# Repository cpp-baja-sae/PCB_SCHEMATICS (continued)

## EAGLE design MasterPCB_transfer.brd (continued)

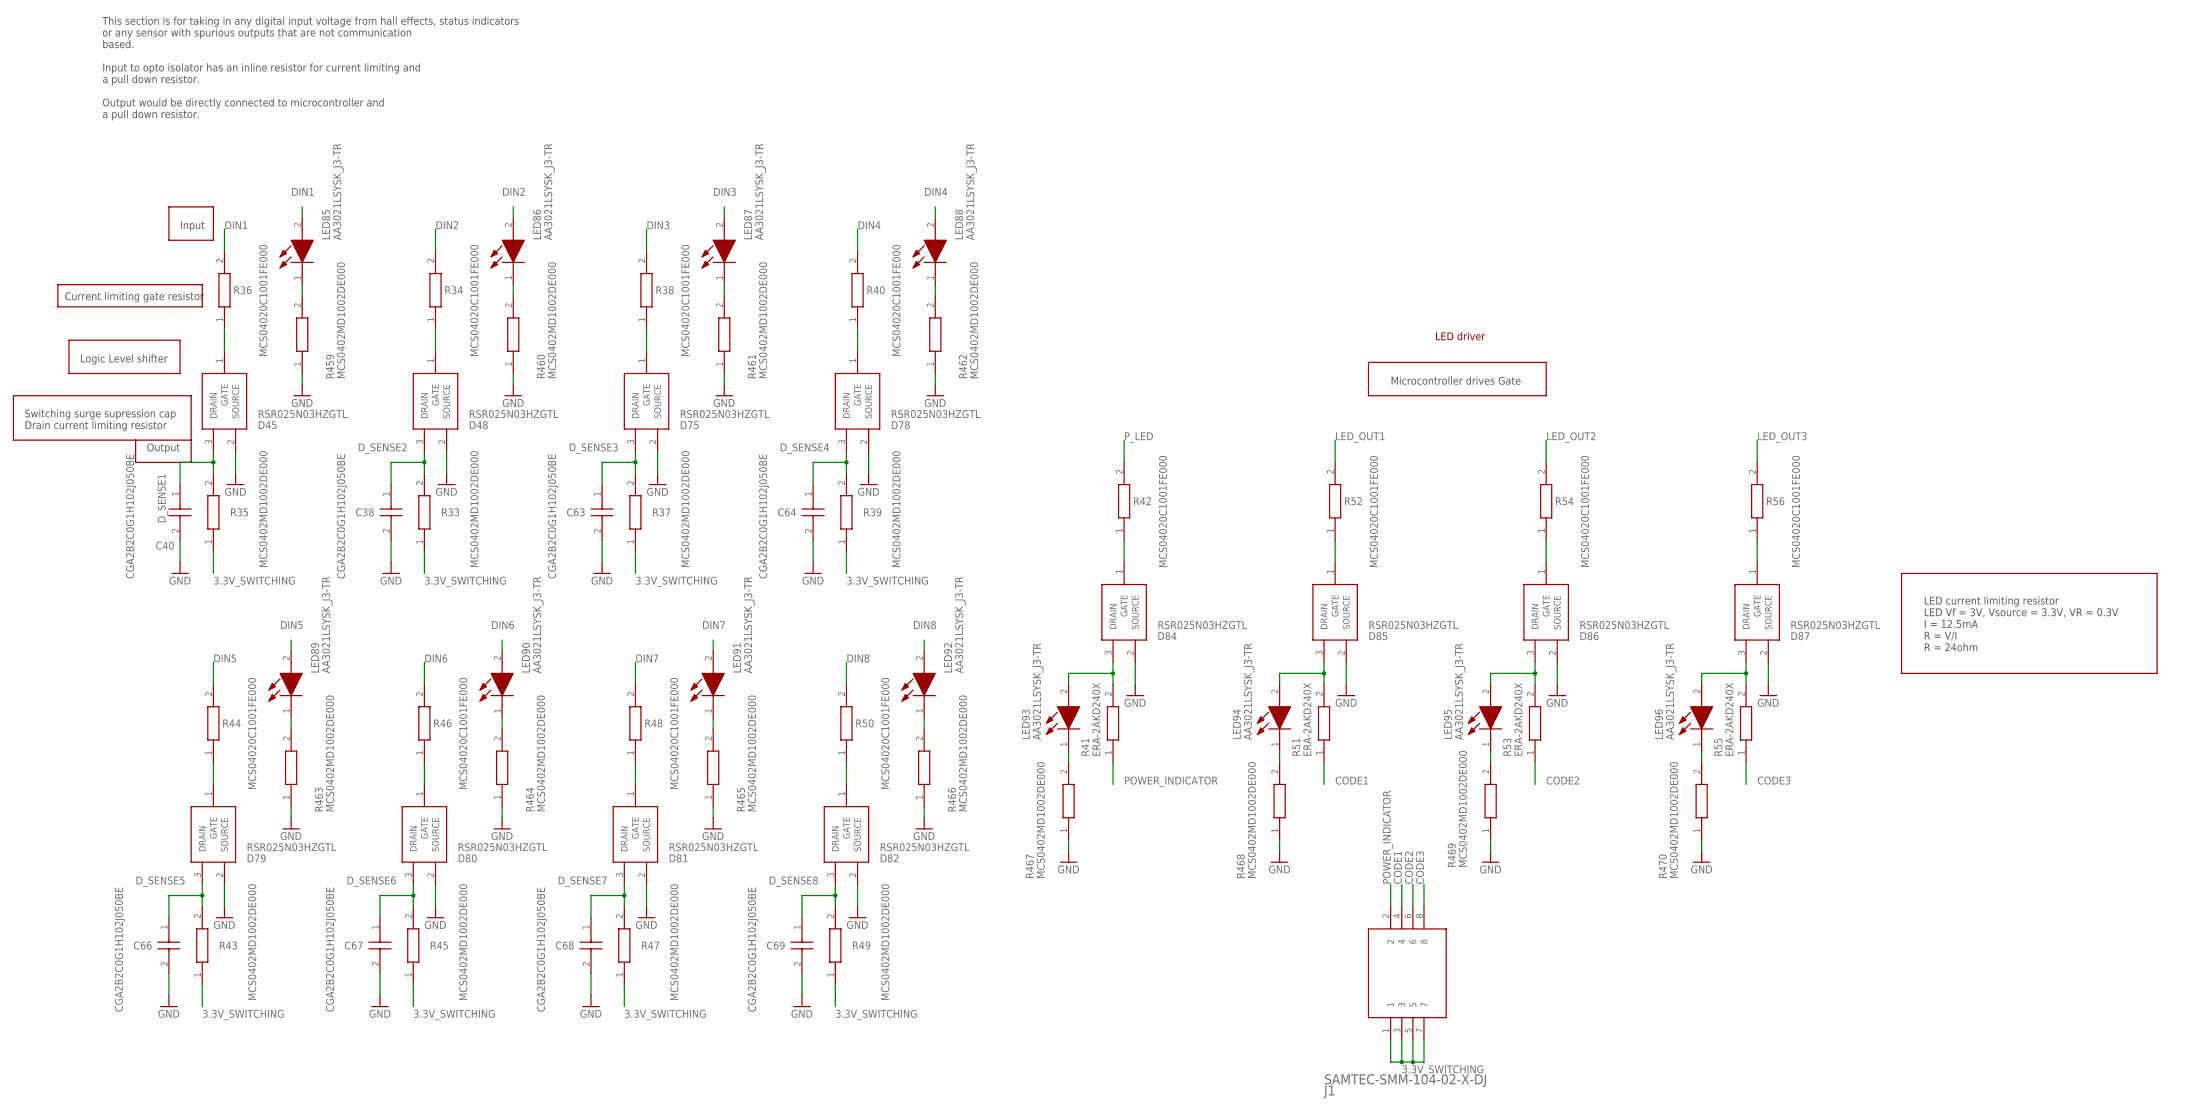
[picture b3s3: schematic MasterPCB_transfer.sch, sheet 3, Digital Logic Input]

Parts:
C38, C40, C63, C64, C66, C67, C68, C69: CGA2B2C0G1H102J050BE; CAPC1005X55N
D45, D48, D75, D78, D79, D80, D81, D82, D84, D85, D86, D87: RSR025N03HZGTL; SOT95P280X100-3N
J1: SAMTEC-SMM-104-02-X-DJ; SAMTEC-SMM-104-02-X-D
LED85, LED86, LED87, LED88, LED89, LED90, LED91, LED92, LED93, LED94, LED95, LED96: AA3021LSYSK_J3-TR; AA3021LSYSKJ3TR
R33, R35, R37, R39, R43, R45, R47, R49, R459, R460, R461, R462, R463, R464, R465, R466, R467, R468, R469, R470: MCS0402MD1002DE000; RESC1005X37N
R34, R36, R38, R40, R42, R44, R46, R48, R50, R52, R54, R56: MCS04020C1001FE000; RESC1005X37N
R41, R51, R53, R55: ERA-2AKD240X; ERA2A_(0402)

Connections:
3.3V_SWITCHING: J1.1, J1.3, J1.5, J1.7, R33.1, R35.1, R37.1, R39.1, R43.1, R45.1, R47.1, R49.1; also elsewhere on the board
CODE1: J1.4, R51.1
CODE2: J1.6, R53.1
CODE3: J1.8, R55.1
DIN1: LED85.2 (A), R36.2; also elsewhere on the board
DIN2: LED86.2 (A), R34.2; also elsewhere on the board
DIN3: LED87.2 (A), R38.2; also elsewhere on the board
DIN4: LED88.2 (A), R40.2; also elsewhere on the board
DIN5: LED89.2 (A), R44.2; also elsewhere on the board
DIN6: LED90.2 (A), R46.2; also elsewhere on the board
DIN7: LED91.2 (A), R48.2; also elsewhere on the board
DIN8: LED92.2 (A), R50.2; also elsewhere on the board
D_SENSE1: C40.1, D45.3 (DRAIN), R35.2; also elsewhere on the board
D_SENSE2: C38.1, D48.3 (DRAIN), R33.2; also elsewhere on the board
D_SENSE3: C63.1, D75.3 (DRAIN), R37.2; also elsewhere on the board
D_SENSE4: C64.1, D78.3 (DRAIN), R39.2; also elsewhere on the board
D_SENSE5: C66.1, D79.3 (DRAIN), R43.2; also elsewhere on the board
D_SENSE6: C67.1, D80.3 (DRAIN), R45.2; also elsewhere on the board
D_SENSE7: C68.1, D81.3 (DRAIN), R47.2; also elsewhere on the board
D_SENSE8: C69.1, D82.3 (DRAIN), R49.2; also elsewhere on the board
GND: C38.2, C40.2, C63.2, C64.2, C66.2, C67.2, C68.2, C69.2, D45.2 (SOURCE), D48.2 (SOURCE), D75.2 (SOURCE), D78.2 (SOURCE), D79.2 (SOURCE), D80.2 (SOURCE), D81.2 (SOURCE), D82.2 (SOURCE), D84.2 (SOURCE), D85.2 (SOURCE), D86.2 (SOURCE), D87.2 (SOURCE), R459.1, R460.1, R461.1, R462.1, R463.1, R464.1, R465.1, R466.1, R467.1, R468.1, R469.1, R470.1; also elsewhere on the board
LED_OUT1: R52.2; also elsewhere on the board
LED_OUT2: R54.2; also elsewhere on the board
LED_OUT3: R56.2; also elsewhere on the board
unnamed: D48.1 (GATE), R34.1
unnamed: D45.1 (GATE), R36.1
unnamed: D84.3 (DRAIN), LED93.2 (A), R41.2
unnamed: D84.1 (GATE), R42.1
unnamed: D75.1 (GATE), R38.1
unnamed: D85.3 (DRAIN), LED94.2 (A), R51.2
unnamed: D78.1 (GATE), R40.1
unnamed: D85.1 (GATE), R52.1
unnamed: D86.3 (DRAIN), LED95.2 (A), R53.2
unnamed: D86.1 (GATE), R54.1
unnamed: D87.3 (DRAIN), LED96.2 (A), R55.2
unnamed: D79.1 (GATE), R44.1
unnamed: D87.1 (GATE), R56.1
unnamed: D80.1 (GATE), R46.1
unnamed: D81.1 (GATE), R48.1
unnamed: D82.1 (GATE), R50.1
unnamed: LED85.1 (K), R459.2
unnamed: LED86.1 (K), R460.2
unnamed: LED93.1 (K), R467.2
unnamed: LED94.1 (K), R468.2
unnamed: LED87.1 (K), R461.2
unnamed: LED95.1 (K), R469.2
unnamed: LED88.1 (K), R462.2
unnamed: LED96.1 (K), R470.2
unnamed: LED89.1 (K), R463.2
unnamed: LED90.1 (K), R464.2
unnamed: LED91.1 (K), R465.2
unnamed: LED92.1 (K), R466.2
POWER_INDICATOR: J1.2, R41.1
P_LED: R42.2; also elsewhere on the board

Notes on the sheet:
This section is for taking in any digital input voltage from hall effects, status indicators or any sensor with spurious outputs that are not communication based. Input to opto isolator has an inline resistor for current limiting and a pull down resistor. Output would be directly connected to micro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
Current limiting gate resistor
Switching surge supression cap Drain current limiting resistor
Logic Level shifter
Output
Input
Microcontroller drives Gate
LED driver
LED current limiting resistor LED Vf = 3V, Vsource = 3.3V, VR = 0.3V I = 12.5mA R = V/I R = 24ohm

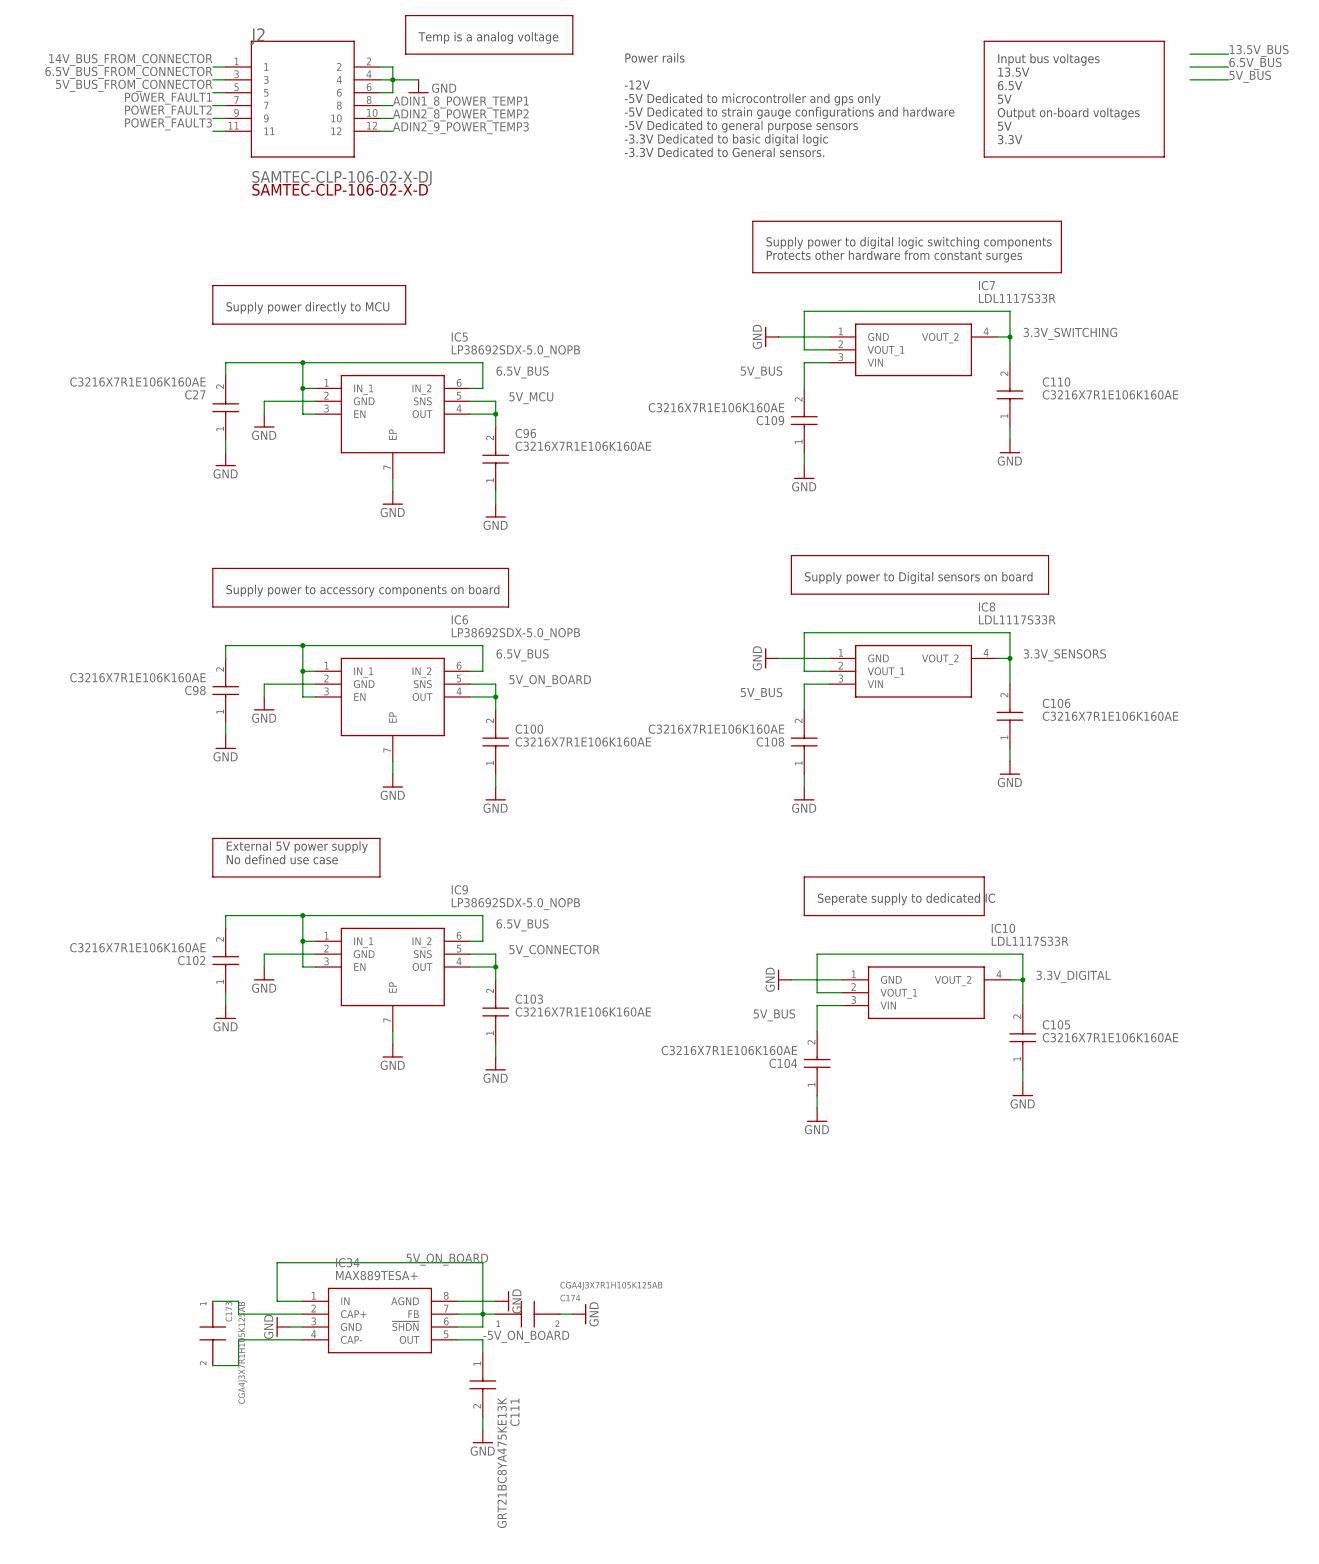
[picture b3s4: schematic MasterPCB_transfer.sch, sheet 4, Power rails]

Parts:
C27, C96, C98, C100, C102, C103, C104, C105, C106, C108, C109, C110: C3216X7R1E106K160AE; C3216_COMMERCIAL
C111: GRT21BC8YA475KE13K; CAPC2012X135N
C173, C174: CGA4J3X7R1H105K125AB; CAPC2012X145N
IC5, IC6, IC9: LP38692SDX-5.0_NOPB; SON95P300X300X80-7N
IC7, IC8, IC10: LDL1117S33R; SOT230P700X180-4N
IC34: MAX889TESA+; SOIC127P600X175-8N
J2: SAMTEC-CLP-106-02-X-DJ; SAMTEC-CLP-106-02-X-D

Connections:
3.3V_DIGITAL: C105.2, IC10.2 (VOUT_1), IC10.4 (VOUT_2); also elsewhere on the board
3.3V_SENSORS: C106.2, IC8.2 (VOUT_1), IC8.4 (VOUT_2); also elsewhere on the board
3.3V_SWITCHING: C110.2, IC7.2 (VOUT_1), IC7.4 (VOUT_2); also elsewhere on the board
5V_BUS: C104.2, C108.2, C109.2, IC7.3 (VIN), IC8.3 (VIN), IC10.3 (VIN); also elsewhere on the board
5V_BUS_FROM_CONNECTOR: J2.5; also elsewhere on the board
5V_CONNECTOR: C103.2, IC9.4 (OUT), IC9.5 (SNS); also elsewhere on the board
5V_MCU: C96.2, IC5.4 (OUT), IC5.5 (SNS); also elsewhere on the board
5V_ON_BOARD: C100.2, C174.1, IC6.4 (OUT), IC6.5 (SNS), IC34.1 (IN), IC34.6 (!SHDN), IC34.7 (FB); also elsewhere on the board
6.5V_BUS: C27.2, C98.2, C102.2, IC5.1 (IN_1), IC5.3 (EN), IC5.6 (IN_2), IC6.1 (IN_1), IC6.3 (EN), IC6.6 (IN_2), IC9.1 (IN_1), IC9.3 (EN), IC9.6 (IN_2); also elsewhere on the board
6.5V_BUS_FROM_CONNECTOR: J2.3; also elsewhere on the board
14V_BUS_FROM_CONNECTOR: J2.1; also elsewhere on the board
-5V_ON_BOARD: C111.1, IC34.5 (OUT); also elsewhere on the board
ADIN1_8_POWER_TEMP1: J2.8; also elsewhere on the board
ADIN2_8_POWER_TEMP2: J2.10; also elsewhere on the board
ADIN2_9_POWER_TEMP3: J2.12; also elsewhere on the board
GND: C27.1, C96.1, C98.1, C100.1, C102.1, C103.1, C104.1, C105.1, C106.1, C108.1, C109.1, C110.1, C111.2, C174.2, IC5.2 (GND), IC5.7 (EP), IC6.2 (GND), IC6.7 (EP), IC7.1 (GND), IC8.1 (GND), IC9.2 (GND), IC9.7 (EP), IC10.1 (GND), IC34.3 (GND), IC34.8 (AGND), J2.2, J2.4, J2.6; also elsewhere on the board
unnamed: C173.1, IC34.2 (CAP+)
unnamed: C173.2, IC34.4 (CAP-)
POWER_FAULT1: J2.7; also elsewhere on the board
POWER_FAULT2: J2.9; also elsewhere on the board
POWER_FAULT3: J2.11; also elsewhere on the board

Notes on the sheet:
Power rails -12V -5V Dedicated to microcontroller and gps only -5V Dedicated to strain gauge configurations and hardware -5V Dedicated to general purpose sensors -3.3V Dedicated to basic digital logic -3.3V Dedicated to General sensors.
Supply power directly to MCU
Supply power to accessory components on board
Supply power to digital logic switching components Protects other hardware from constant surges
Supply power to Digital sensors on board
External 5V power supply No defined use case
Seperate supply to dedicated IC
Input bus voltages 13.5V 6.5V 5V Output on-board voltages 5V 3.3V
Temp is a analog voltage

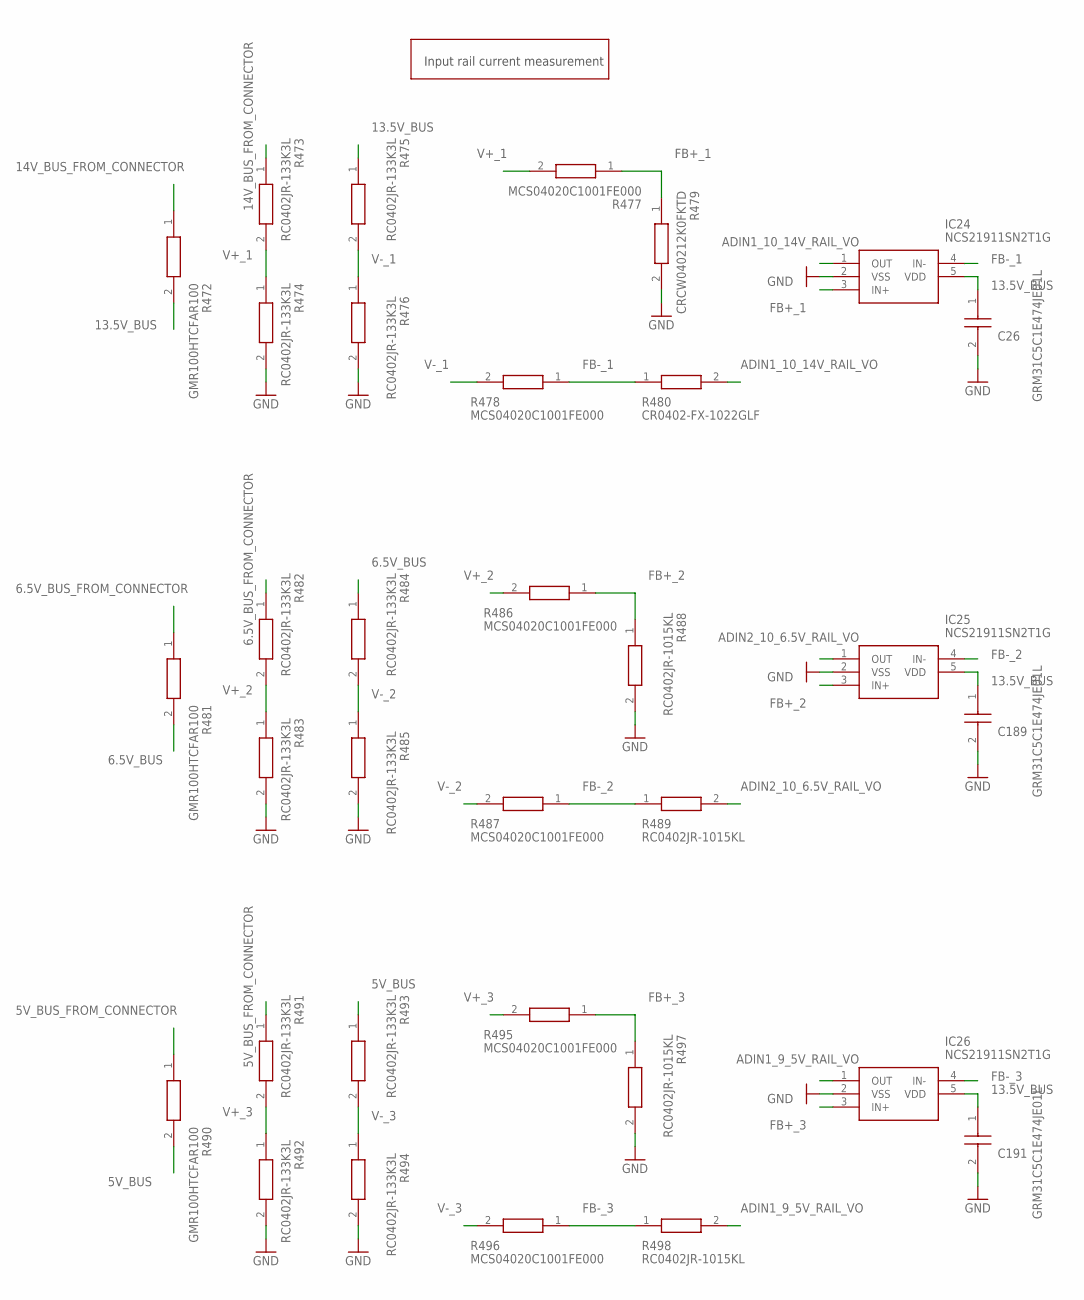
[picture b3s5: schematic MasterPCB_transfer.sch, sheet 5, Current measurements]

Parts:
C26, C189, C191: GRM31C5C1E474JE01L; CAPC3216X180N
IC24, IC25, IC26: NCS21911SN2T1G; SOT95P275X110-5N
R472, R481, R490: GMR100HTCFAR100; RESC6432X55N
R473, R474, R475, R476, R482, R483, R484, R485, R491, R492, R493, R494: RC0402JR-133K3L; RESC1005X40N
R477, R478, R486, R487, R495, R496: MCS04020C1001FE000; RESC1005X37N
R479: CRCW040212K0FKTD; RESC1005X40N
R480: CR0402-FX-1022GLF; RESC1005X40N
R488, R489, R497, R498: RC0402JR-1015KL; RESC1005X40N

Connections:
5V_BUS: R490.2, R493.1; also elsewhere on the board
5V_BUS_FROM_CONNECTOR: R490.1, R491.1; also elsewhere on the board
6.5V_BUS: R481.2, R484.1; also elsewhere on the board
6.5V_BUS_FROM_CONNECTOR: R481.1, R482.1; also elsewhere on the board
13.5V_BUS: C26.1, C189.1, C191.1, IC24.5 (VDD), IC25.5 (VDD), IC26.5 (VDD), R472.2, R475.1; also elsewhere on the board
14V_BUS_FROM_CONNECTOR: R472.1, R473.1; also elsewhere on the board
ADIN1_9_5V_RAIL_VO: IC26.1 (OUT), R498.2; also elsewhere on the board
ADIN1_10_14V_RAIL_VO: IC24.1 (OUT), R480.2; also elsewhere on the board
ADIN2_10_6.5V_RAIL_VO: IC25.1 (OUT), R489.2; also elsewhere on the board
FB+_1: IC24.3 (IN+), R477.1, R479.1
FB+_2: IC25.3 (IN+), R486.1, R488.1
FB+_3: IC26.3 (IN+), R495.1, R497.1
FB-_1: IC24.4 (IN-), R478.1, R480.1
FB-_2: IC25.4 (IN-), R487.1, R489.1
FB-_3: IC26.4 (IN-), R496.1, R498.1
GND: C26.2, C189.2, C191.2, IC24.2 (VSS), IC25.2 (VSS), IC26.2 (VSS), R474.2, R476.2, R479.2, R483.2, R485.2, R488.2, R492.2, R494.2, R497.2; also elsewhere on the board
V+_1: R473.2, R474.1, R477.2
V+_2: R482.2, R483.1, R486.2
V+_3: R491.2, R492.1, R495.2
V-_1: R475.2, R476.1, R478.2
V-_2: R484.2, R485.1, R487.2
V-_3: R493.2, R494.1, R496.2

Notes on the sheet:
Input rail current measurement

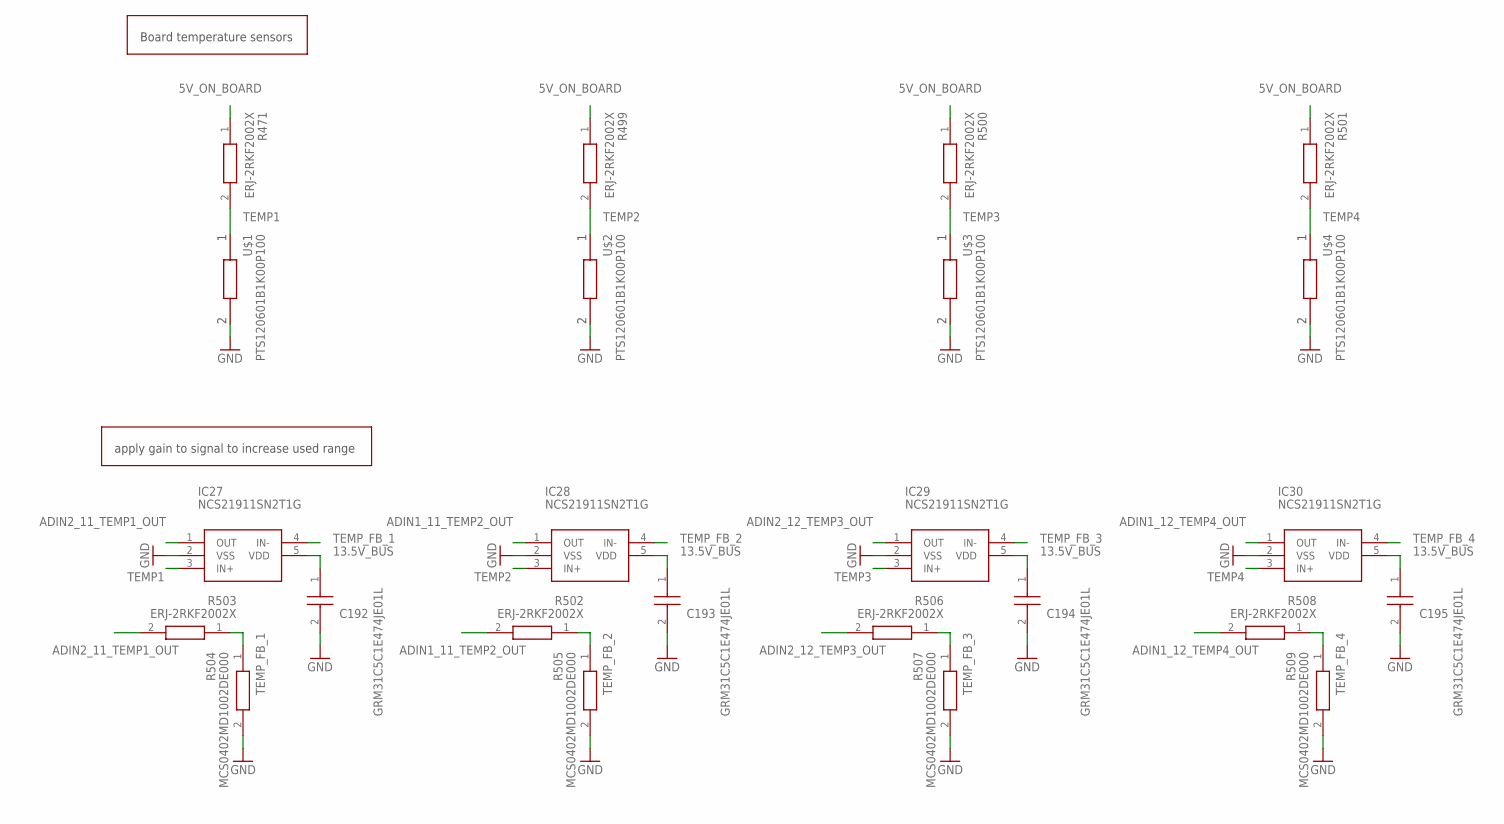
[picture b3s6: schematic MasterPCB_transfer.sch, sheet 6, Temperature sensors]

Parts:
C192, C193, C194, C195: GRM31C5C1E474JE01L; CAPC3216X180N
IC27, IC28, IC29, IC30: NCS21911SN2T1G; SOT95P275X110-5N
R471, R499, R500, R501, R502, R503, R506, R508: ERJ-2RKF2002X; ERJ2R_(0402)
R504, R505, R507, R509: MCS0402MD1002DE000; RESC1005X37N
U$1, U$2, U$3, U$4: PTS120601B1K00P100; RESC3016X70N

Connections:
5V_ON_BOARD: R471.1, R499.1, R500.1, R501.1; also elsewhere on the board
13.5V_BUS: C192.1, C193.1, C194.1, C195.1, IC27.5 (VDD), IC28.5 (VDD), IC29.5 (VDD), IC30.5 (VDD); also elsewhere on the board
ADIN1_11_TEMP2_OUT: IC28.1 (OUT), R502.2; also elsewhere on the board
ADIN1_12_TEMP4_OUT: IC30.1 (OUT), R508.2; also elsewhere on the board
ADIN2_11_TEMP1_OUT: IC27.1 (OUT), R503.2; also elsewhere on the board
ADIN2_12_TEMP3_OUT: IC29.1 (OUT), R506.2; also elsewhere on the board
GND: C192.2, C193.2, C194.2, C195.2, IC27.2 (VSS), IC28.2 (VSS), IC29.2 (VSS), IC30.2 (VSS), R504.2, R505.2, R507.2, R509.2, U$1.2, U$2.2, U$3.2, U$4.2; also elsewhere on the board
TEMP1: IC27.3 (IN+), R471.2, U$1.1
TEMP2: IC28.3 (IN+), R499.2, U$2.1
TEMP3: IC29.3 (IN+), R500.2, U$3.1
TEMP4: IC30.3 (IN+), R501.2, U$4.1
TEMP_FB_1: IC27.4 (IN-), R503.1, R504.1
TEMP_FB_2: IC28.4 (IN-), R502.1, R505.1
TEMP_FB_3: IC29.4 (IN-), R506.1, R507.1
TEMP_FB_4: IC30.4 (IN-), R508.1, R509.1

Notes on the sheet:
Board temperature sensors
apply gain to signal to increase used range

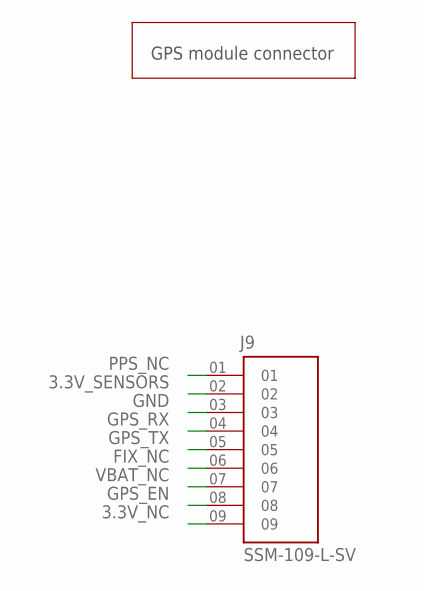
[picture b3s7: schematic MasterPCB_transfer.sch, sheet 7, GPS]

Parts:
J9: SSM-109-L-SV; SAMTEC_SSM-109-L-SV

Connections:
3.3V_NC: J9.09
3.3V_SENSORS: J9.02; also elsewhere on the board
FIX_NC: J9.06
GND: J9.03; also elsewhere on the board
GPS_EN: J9.08; also elsewhere on the board
GPS_RX: J9.04; also elsewhere on the board
GPS_TX: J9.05; also elsewhere on the board
PPS_NC: J9.01
VBAT_NC: J9.07

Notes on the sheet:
GPS module connector

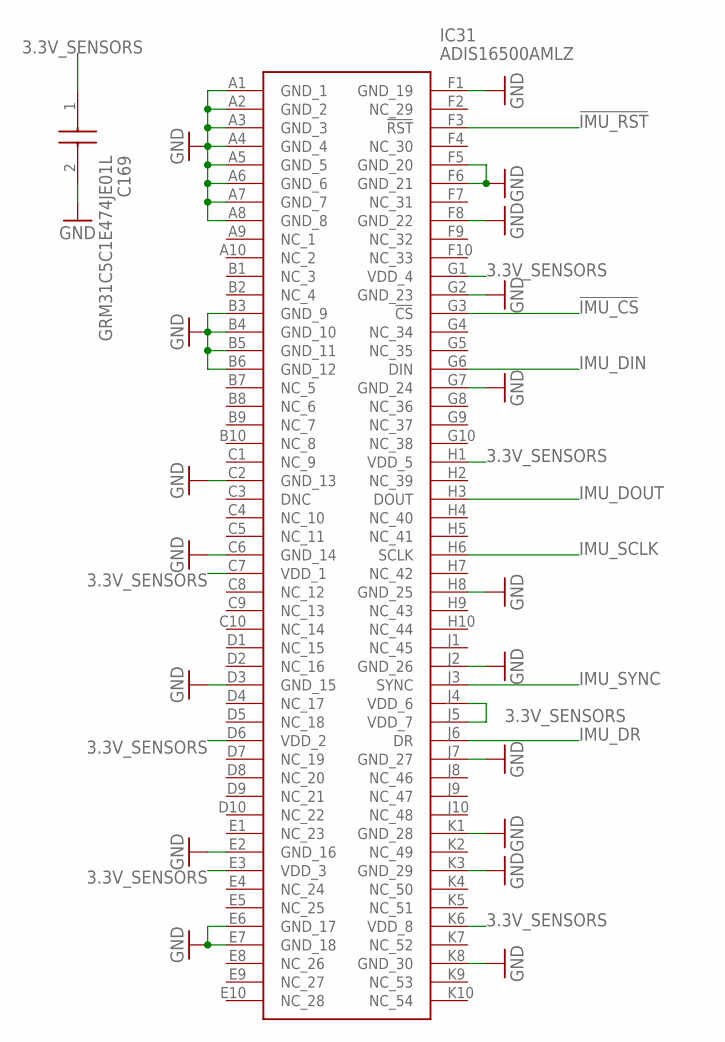
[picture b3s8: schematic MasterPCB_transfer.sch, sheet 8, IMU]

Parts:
C169: GRM31C5C1E474JE01L; CAPC3216X180N
IC31: ADIS16500AMLZ; BGA100C127P10X10_1500X1500X608

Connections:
3.3V_SENSORS: C169.1, IC31.C7 (VDD_1), IC31.D6 (VDD_2), IC31.E3 (VDD_3), IC31.G1 (VDD_4), IC31.H1 (VDD_5), IC31.J4 (VDD_6), IC31.J5 (VDD_7), IC31.K6 (VDD_8); also elsewhere on the board
!IMU_CS: IC31.G3 (!CS); also elsewhere on the board
!IMU_RST: IC31.F3 (!RST); also elsewhere on the board
GND: C169.2, IC31.A1 (GND_1), IC31.A2 (GND_2), IC31.A3 (GND_3), IC31.A4 (GND_4), IC31.A5 (GND_5), IC31.A6 (GND_6), IC31.A7 (GND_7), IC31.A8 (GND_8), IC31.B3 (GND_9), IC31.B4 (GND_10), IC31.B5 (GND_11), IC31.B6 (GND_12), IC31.C2 (GND_13), IC31.C6 (GND_14), IC31.D3 (GND_15), IC31.E2 (GND_16), IC31.E6 (GND_17), IC31.E7 (GND_18), IC31.F1 (GND_19), IC31.F5 (GND_20), IC31.F6 (GND_21), IC31.F8 (GND_22), IC31.G2 (GND_23), IC31.G7 (GND_24), IC31.H8 (GND_25), IC31.J2 (GND_26), IC31.J7 (GND_27), IC31.K1 (GND_28), IC31.K3 (GND_29), IC31.K8 (GND_30); also elsewhere on the board
IMU_DIN: IC31.G6 (DIN); also elsewhere on the board
IMU_DOUT: IC31.H3 (DOUT); also elsewhere on the board
IMU_DR: IC31.J6 (DR); also elsewhere on the board
IMU_SCLK: IC31.H6 (SCLK); also elsewhere on the board
IMU_SYNC: IC31.J3 (SYNC); also elsewhere on the board

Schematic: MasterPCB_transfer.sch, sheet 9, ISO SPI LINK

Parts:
C170: GRM31C5C1E474JE01L; CAPC3216X180N
C171, C172: 06035C270JAT2A; CAPC1608X90N
IC32: LTC6820IUD#PBF; QFN50P300X300X80-17N
IC33: CBTL01023GM,115; QFN50P200X155X50-10N
R510: CPF0402B1K21E1; RESC1005X35N
R511: ERA-2AEB7870X; ERA2AED122X
R512: TNPW0402100RBYEP; RESC1005X40N
R513, R514, R515, R516: CRG0402ZR; RESC1005X40N
T1: 782482_33VC; DIP1016W60P254L914H635Q6N

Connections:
3.3V_DIGITAL: C170.1, IC32.5 (VDDS), IC32.6 (POL), IC32.7 (PHA), IC32.8 (VDD), IC32.11 (MSTR), IC32.16 (EN); also elsewhere on the board
3.3V_SENSORS: IC33.5 (VDD); also elsewhere on the board
!ISO_CS: IC32.4 (!CS); also elsewhere on the board
GND: C170.2, C171.2, C172.2, IC32.13 (GND), IC32.17 (EP), IC33.10 (GND), R511.2; also elsewhere on the board
IBAIS: IC32.15 (IBIAS), R510.1
ICMP: IC32.14 (ICMP), R510.2, R511.1
IM_INPUT: IC32.9 (IM), R512.2, T1.3 (PRIMARY_3)
IM_OUT1: IC33.8 (B_N), R516.1; also elsewhere on the board
IM_OUT2: IC33.6 (C_N); also elsewhere on the board
IM_OUTPUT: R514.2, R516.2, T1.4 (SECONDARY_1)
IP_INPUT: IC32.10 (IP), R512.1, T1.1 (PRIMARY_1)
IP_OUT1: IC33.9 (B_P), R515.1; also elsewhere on the board
IP_OUT2: IC33.7 (C_P); also elsewhere on the board
IP_OUTPUT: R513.2, R515.2, T1.6 (SECONDARY_3)
ISO_MISO: IC32.2 (MISO); also elsewhere on the board
ISO_MOSI: IC32.1 (MOSI); also elsewhere on the board
ISO_SPI_CH_SEL: IC33.4 (SEL); also elsewhere on the board
ISO_SPI_HIGH_Z_SWITCH: IC33.1 (XSD); also elsewhere on the board
ISO_SPI_SCLK: IC32.3 (SCK); also elsewhere on the board
ISO_SPI_SLOW: IC32.12 (SLOW); also elsewhere on the board
unnamed: IC33.2 (A_P), R513.1
unnamed: IC33.3 (A_N), R514.1
unnamed: C171.1, T1.2 (PRIMARY_2)
unnamed: C172.1, T1.5 (SECONDARY_2)

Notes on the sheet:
Manual disconnect between dual and single driver operation Priority is 40G accelerometer connection Enable direct connection with 40G link

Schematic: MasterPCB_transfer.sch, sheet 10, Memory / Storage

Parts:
J3: MEM2051-00-195-00-A; MEM20510019500A

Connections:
3.3V_DIGITAL: J3.P4 (VDD); also elsewhere on the board
FLASH_CD/DAT3_SPI-CS: J3.P2 (CD/DAT3); also elsewhere on the board
FLASH_CLK: J3.P5 (CLK); also elsewhere on the board
FLASH_CMD_SPI-DI: J3.P3 (CMD); also elsewhere on the board
FLASH_DAT0_SPI-DO: J3.P7 (DAT0); also elsewhere on the board
FLASH_DAT1: J3.P8 (DAT1); also elsewhere on the board
FLASH_DAT2: J3.P1 (DAT2); also elsewhere on the board
GND: J3.P6 (VSS); also elsewhere on the board
